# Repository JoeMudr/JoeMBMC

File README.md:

# JoeM BMC
Originally called "JoeM BMS" is now called "JoeM BMC" Battery Management Controller. Since it's not a complete BMS but only a controller for existing BMS-Modules.
This is the updated version for Teensy 4.0

This project is derived from [Toms SimpBMS code](https://github.com/Tom-evnut). It started as a clone (Software & Hardware) but ended up completely rewritten and redesigned. But you might still find some traces to the original code.

Complete documentation coming soon.

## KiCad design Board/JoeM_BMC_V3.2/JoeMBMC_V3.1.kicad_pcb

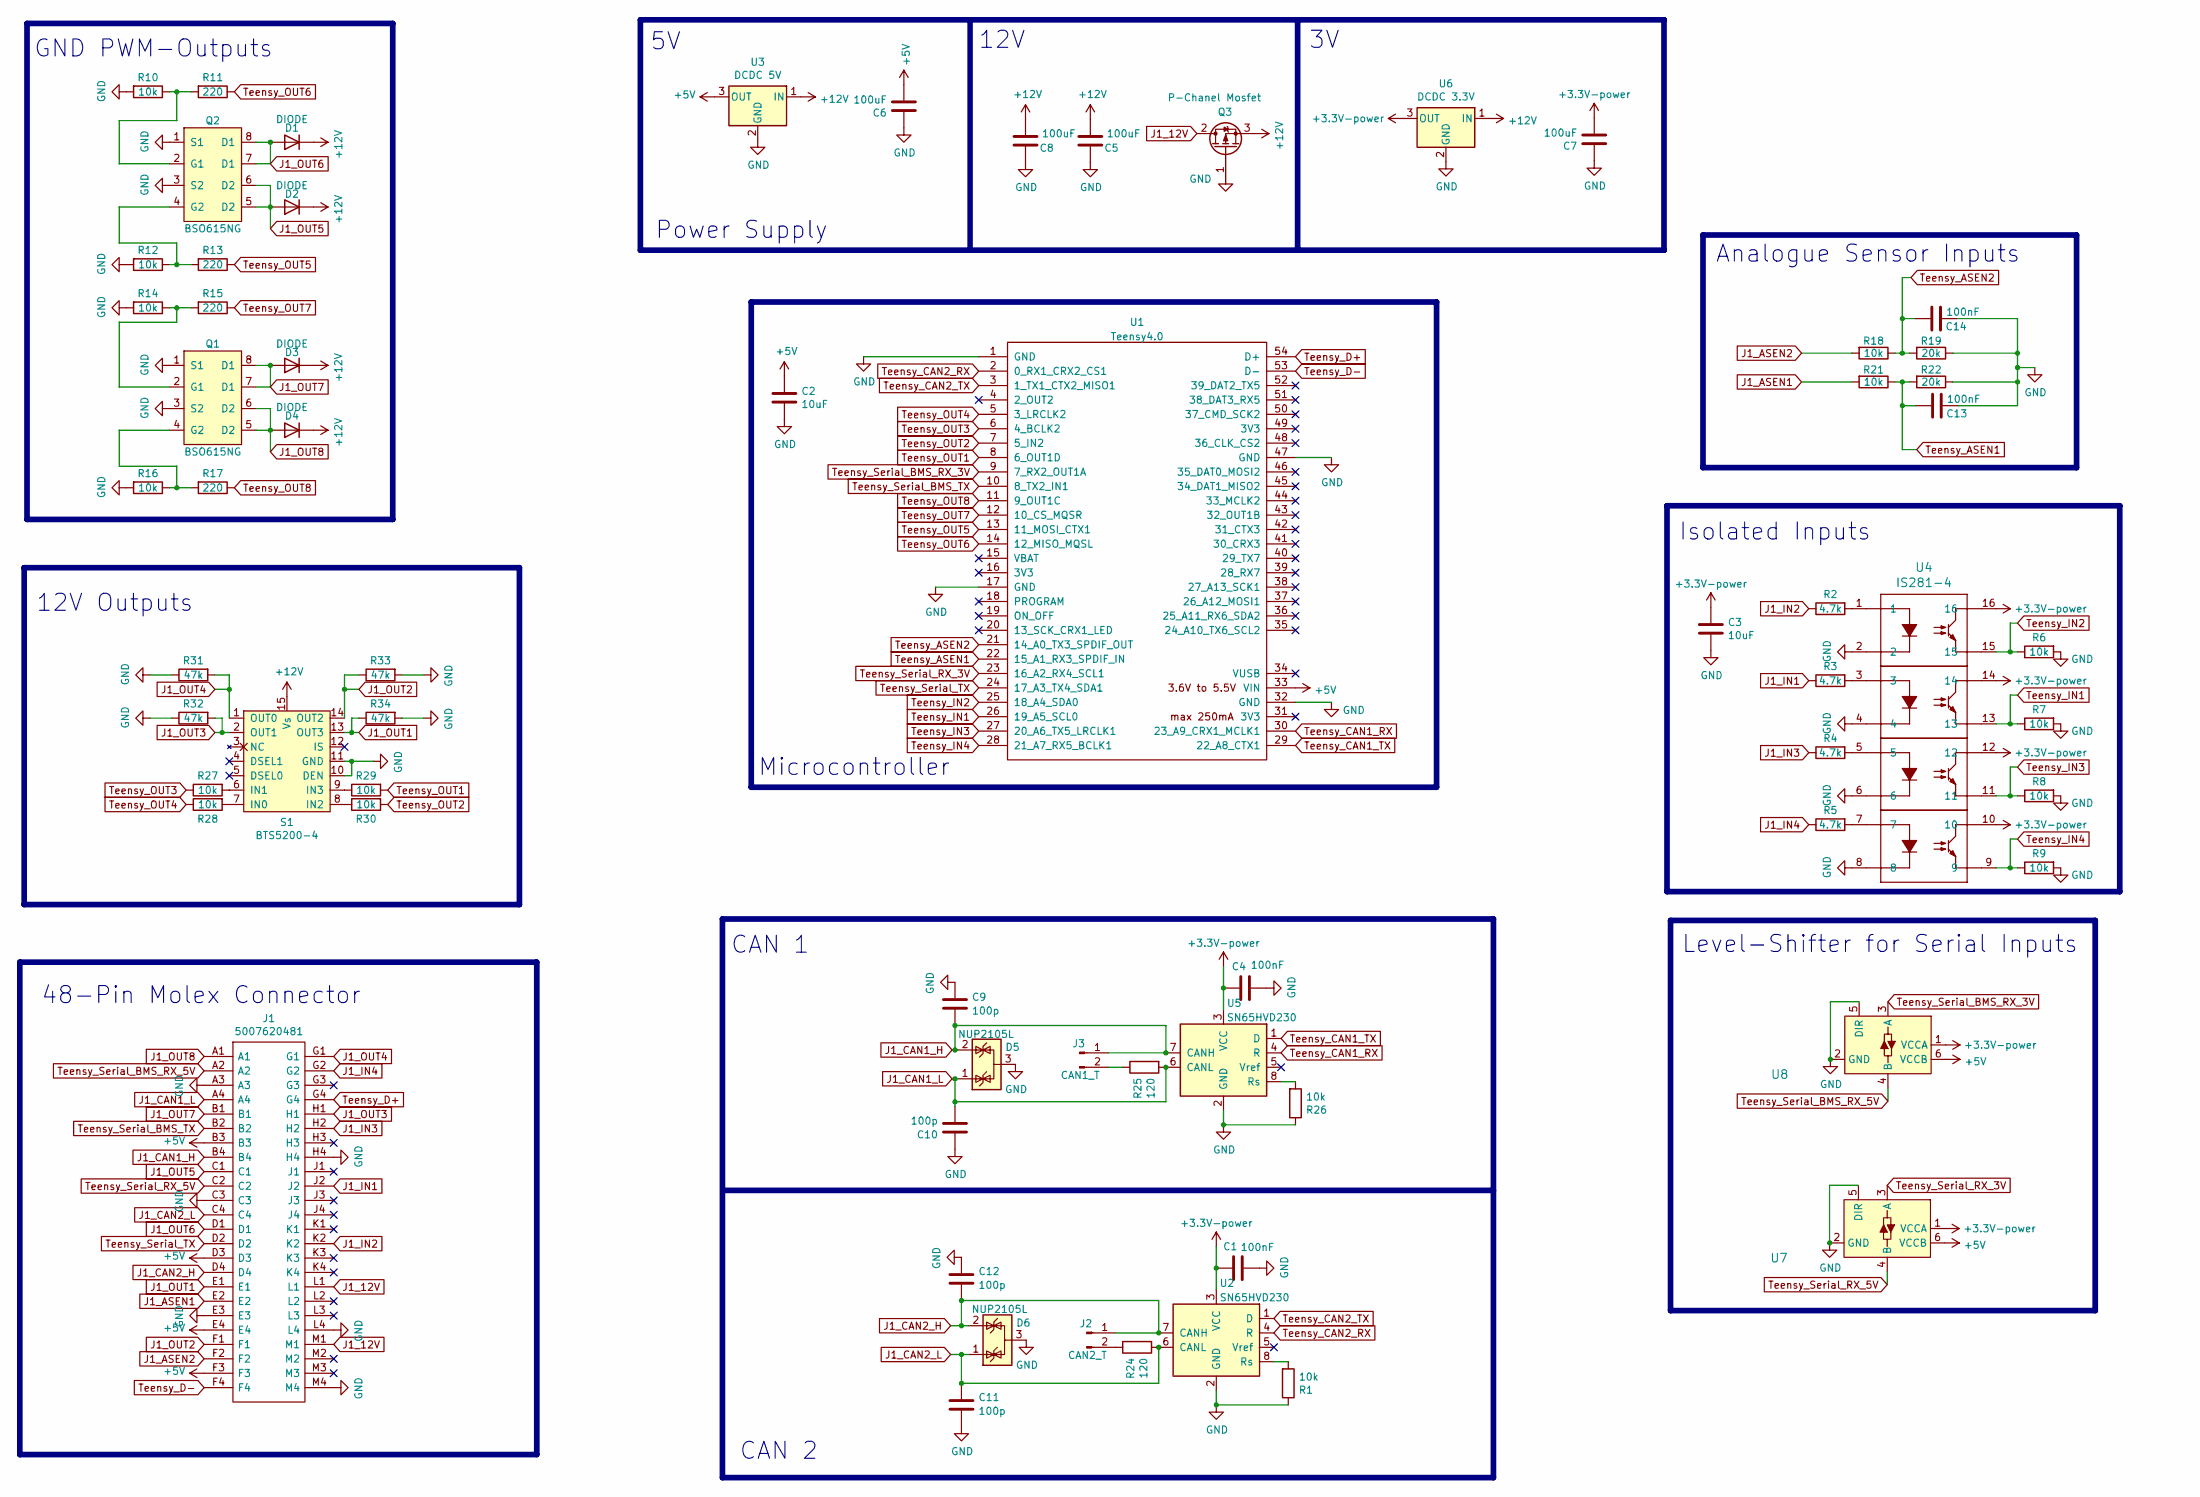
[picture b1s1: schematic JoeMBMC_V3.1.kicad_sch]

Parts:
C1, C4, C13, C14: 100nF; C_0805_2012Metric; LCSC C49678
C2, C3: 10uF; C_0805_2012Metric; LCSC C15850
C5, C6, C7, C8: 100uF; C_Elec_6.3x7.7; LCSC C3001246
C9, C10, C11, C12: 100p; C_0402_1005Metric; LCSC C1546
D1, D2, D3, D4: DIODE; D_SOD-123F; LCSC C8598
D5, D6: NUP2105L; SOT-23; LCSC C284104
J1: 5007620481; Manufacturer_Part_Number 5007620481
J2: CAN2_T; PinHeader_1x02_P2.54mm_Vertical
J3: CAN1_T; PinHeader_1x02_P2.54mm_Vertical
Q1, Q2: BSO615NG; SO-8_IRF956; LCSC C693398
Q3: P-Chanel Mosfet; TO-252-2; LCSC C416264
R1, R6, R7, R8, R9, R10, R12, R14, R16, R18, R21, R26, R27, R28, R29, R30: 10k; R_0805_2012Metric; LCSC C17414
R2, R3, R4, R5: 4.7k; R_0805_2012Metric; LCSC C17673
R11, R13, R15, R17: 220; R_0805_2012Metric; LCSC C17557
R19, R22: 20k; R_0805_2012Metric; LCSC C4328
R24, R25: 120; R_0805_2012Metric; LCSC C17437
R31, R32, R33, R34: 47k; R_0805_2012Metric; LCSC C17713
S1: BTS5200-4; PG-DSO-14-40_EP; LCSC C534815
U1: Teensy4.0; Teensy40_JoeMBMS
U2, U5: SN65HVD230; SOIC-8_3.9x4.9mm_P1.27mm; LCSC C12084
U3: DCDC 5V; Converter_DCDC_RECOM_R-78E-0.5_THT
U4: IS281-4; TLP293-4; LCSC C89878
U6: DCDC 3.3V; Converter_DCDC_RECOM_R-78E-0.5_THT
U7, U8: Level Shifter 5V to 3V; SOT-23-6; LCSC C7843

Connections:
+3V3: C1.2, C3.2, C4.2, C7.1, U2.3 (VCC), U4.10, U4.12, U4.14, U4.16, U5.3 (VCC), U6.3 (OUT), U7.1 (VCCA), U8.1 (VCCA); also elsewhere on the board
+5V: C2.2, C6.1, J1.B3, J1.D3, J1.E4, J1.F3, U1.33 (VIN), U3.3 (OUT), U7.6 (VCCB), U8.6 (VCCB); also elsewhere on the board
+12V: C5.1, C8.1, D1.1 (K), D2.1 (K), D3.1 (K), D4.1 (K), Q3.3 (S), S1.15 (Vs), U3.1 (IN), U6.1 (IN); also elsewhere on the board
GND: C1.1, C2.1, C3.1, C4.1, C5.2, C6.2, C7.2, C8.2, C9.1, C10.1, C11.2, C12.1, C13.1, C14.1, D5.3 (A), D6.3 (A), J1.A3, J1.C3, J1.E3, J1.H4, J1.L4, J1.M4, Q1.1 (S1), Q1.3 (S2), Q2.1 (S1), Q2.3 (S2), Q3.1 (G), R1.1, R6.2, R7.2, R8.2, R9.2, R10.2, R12.2, R14.2, R16.2, R19.1, R22.1, R26.1, R31.1, R32.1, R33.2, R34.2, S1.10 (DEN), S1.11 (GND), U1.1 (GND), U1.17 (GND), U1.32 (GND), U1.47 (GND), U2.2 (GND), U3.2 (GND), U4.2, U4.4, U4.6, U4.8, U5.2 (GND), U6.2 (GND), U7.2 (GND), U7.5 (DIR), U8.2 (GND), U8.5 (DIR)
J1_12V: J1.L1, J1.M1, Q3.2 (D)
J1_ASEN1: J1.E2, R21.2
J1_ASEN2: J1.F2, R18.2
J1_CAN1_H: C9.2, D5.2 (K), J1.B4, J3.1, U5.7 (CANH)
J1_CAN1_L: C10.2, D5.1 (K), J1.A4, R25.2, U5.6 (CANL)
J1_CAN2_H: C12.2, D6.2 (K), J1.D4, J2.1, U2.7 (CANH)
J1_CAN2_L: C11.1, D6.1 (K), J1.C4, R24.2, U2.6 (CANL)
J1_IN1: J1.J2, R3.1
J1_IN2: J1.K2, R2.1
J1_IN3: J1.H2, R4.1
J1_IN4: J1.G2, R5.1
J1_OUT1: J1.E1, R34.1, S1.13 (OUT3)
J1_OUT2: J1.F1, R33.1, S1.14 (OUT2)
J1_OUT3: J1.H1, R32.2, S1.2 (OUT1)
J1_OUT4: J1.G1, R31.2, S1.1 (OUT0)
J1_OUT5: D2.2 (A), J1.C1, Q2.5 (D2), Q2.6 (D2)
J1_OUT6: D1.2 (A), J1.D1, Q2.7 (D1), Q2.8 (D1)
J1_OUT7: D3.2 (A), J1.B1, Q1.7 (D1), Q1.8 (D1)
J1_OUT8: D4.2 (A), J1.A1, Q1.5 (D2), Q1.6 (D2)
unnamed: J2.2, R24.1
unnamed: J3.2, R25.1
unnamed: Q1.2 (G1), R14.1, R15.2
unnamed: Q1.4 (G2), R16.1, R17.2
unnamed: Q2.2 (G1), R10.1, R11.2
unnamed: Q2.4 (G2), R12.1, R13.2
unnamed: R2.2, U4.1
unnamed: R3.2, U4.3
unnamed: R4.2, U4.5
unnamed: R5.2, U4.7
unnamed: R28.2, S1.7 (IN0)
unnamed: R27.2, S1.6 (IN1)
unnamed: R30.1, S1.8 (IN2)
unnamed: R29.1, S1.9 (IN3)
unnamed: R1.2, U2.8 (Rs)
unnamed: R26.2, U5.8 (Rs)
Teensy_ASEN1: C13.2, R21.1, R22.2, U1.22 (15_A1_RX3_SPDIF_IN)
Teensy_ASEN2: C14.2, R18.1, R19.2, U1.21 (14_A0_TX3_SPDIF_OUT)
Teensy_CAN1_RX: U1.30 (23_A9_CRX1_MCLK1), U5.4 (R)
Teensy_CAN1_TX: U1.29 (22_A8_CTX1), U5.1 (D)
Teensy_CAN2_RX: U1.2 (0_RX1_CRX2_CS1), U2.4 (R)
Teensy_CAN2_TX: U1.3 (1_TX1_CTX2_MISO1), U2.1 (D)
Teensy_D+: J1.G4, U1.54 (D+)
Teensy_D-: J1.F4, U1.53 (D-)
Teensy_IN1: R7.1, U1.26 (19_A5_SCL0), U4.13
Teensy_IN2: R6.1, U1.25 (18_A4_SDA0), U4.15
Teensy_IN3: R8.1, U1.27 (20_A6_TX5_LRCLK1), U4.11
Teensy_IN4: R9.1, U1.28 (21_A7_RX5_BCLK1), U4.9
Teensy_OUT1: R29.2, U1.8 (6_OUT1D)
Teensy_OUT2: R30.2, U1.7 (5_IN2)
Teensy_OUT3: R27.1, U1.6 (4_BCLK2)
Teensy_OUT4: R28.1, U1.5 (3_LRCLK2)
Teensy_OUT5: R13.1, U1.13 (11_MOSI_CTX1)
Teensy_OUT6: R11.1, U1.14 (12_MISO_MQSL)
Teensy_OUT7: R15.1, U1.12 (10_CS_MQSR)
Teensy_OUT8: R17.1, U1.11 (9_OUT1C)
Teensy_Serial_BMS_RX_3V: U1.9 (7_RX2_OUT1A), U8.3 (A)
Teensy_Serial_BMS_RX_5V: J1.A2, U8.4 (B)
Teensy_Serial_BMS_TX: J1.B2, U1.10 (8_TX2_IN1)
Teensy_Serial_RX_3V: U1.23 (16_A2_RX4_SCL1), U7.3 (A)
Teensy_Serial_RX_5V: J1.C2, U7.4 (B)
Teensy_Serial_TX: J1.D2, U1.24 (17_A3_TX4_SDA1)

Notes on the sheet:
Analogue Sensor Inputs
GND PWM-Outputs
48-Pin Molex Connector
CAN 2
CAN 1
12V Outputs
Isolated Inputs
Microcontroller
Power Supply
12V
Level-Shifter for Serial Inputs

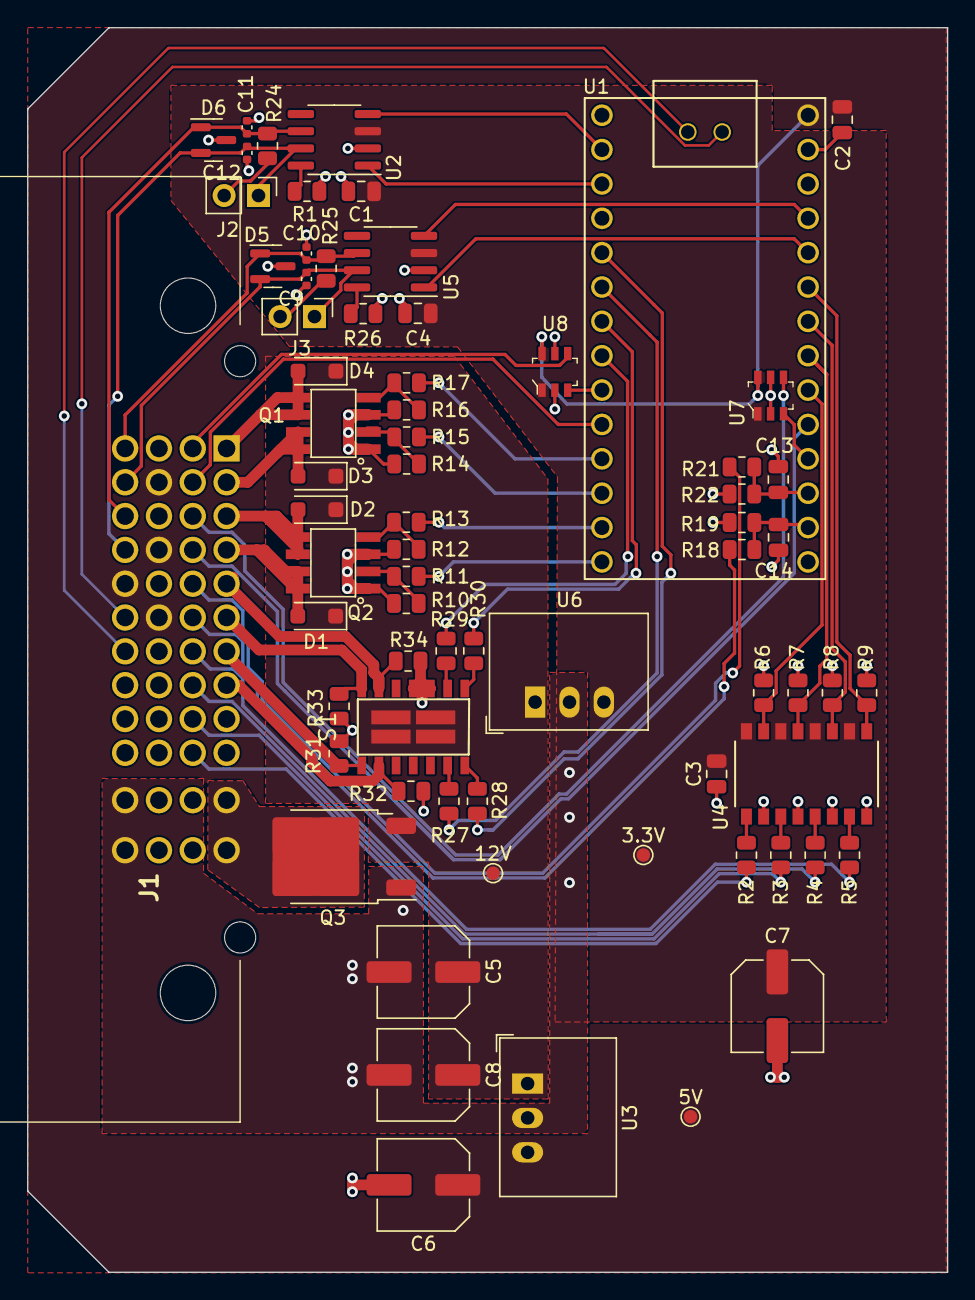
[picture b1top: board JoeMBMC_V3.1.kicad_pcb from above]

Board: 2 copper layers, 68.0 x 92.0 mm, 70 parts (0 on the bottom side), 65 nets.

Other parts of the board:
3.3V, 5V, 12V: TestPoint_Pad_D1.0mm

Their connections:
+3V3: 3.3V.1; also elsewhere on the board
+5V: 5V.1; also elsewhere on the board
+12V: 12V.1; also elsewhere on the board

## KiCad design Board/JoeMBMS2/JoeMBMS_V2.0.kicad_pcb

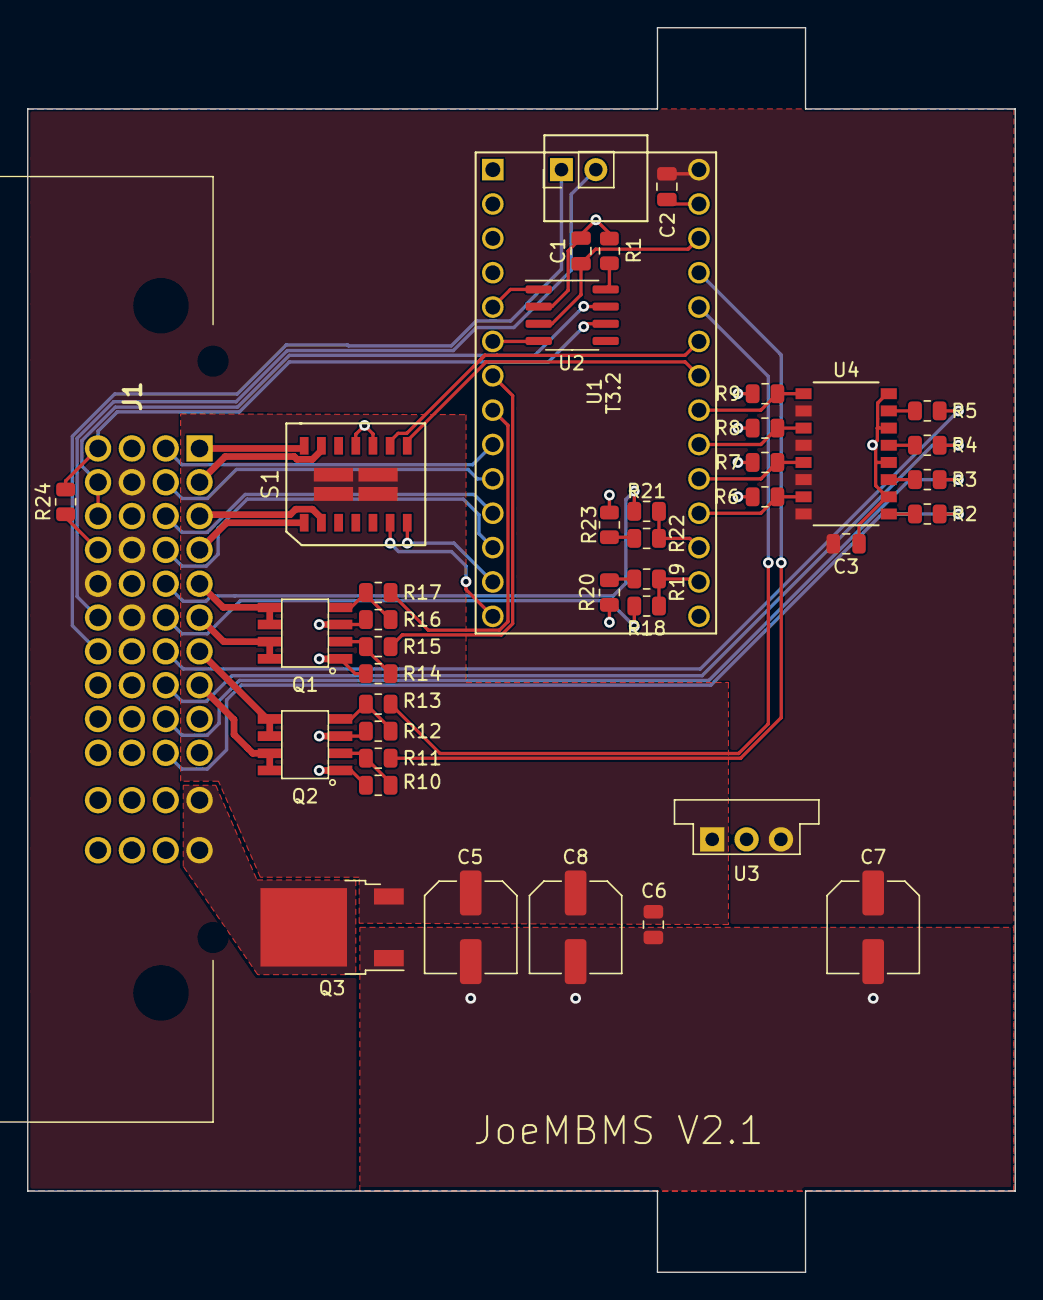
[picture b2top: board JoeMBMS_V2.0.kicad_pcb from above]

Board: 2 copper layers, 73.0 x 92.0 mm, 40 parts (0 on the bottom side), 53 nets.

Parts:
C1: 100nF; C_0805_2012Metric
C2, C3, C6: 10uF; C_0805_2012Metric
C5, C7, C8: 100uF; C_Elec_6.3x7.7
J1: 5007620481
Q1, Q2: BSO615NG; SO-8_IRF956
Q3: P-Chanel Mosfet; TO-252-2
R1, R6, R7, R8, R9, R10, R12, R14, R16, R18, R19, R20, R21, R22, R23: 10k; R_0805_2012Metric
R2, R3, R4, R5: 4.7k; R_0805_2012Metric
R11, R13, R15, R17: 220; R_0805_2012Metric
R24: 120; R_0805_2012Metric
S1: BTS5200-4; PG-DSO-14-40_EP
U1: Teensy3.2; Teensy30_31_32_LC_Mod
U2: SN65HVD230; SOIC-8_3.9x4.9mm_P1.27mm
U3: DCDC 5V; Converter_DCDC_muRata_OKI-78SR_Vertical
U4: IS281-4; TLP293-4

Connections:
+3V3: C1.2, U1.31, U2.3
+12V: C5.1, C6.2, C8.1, Q3.3, S1.15, U3.1
GND: C1.1, C2.1, C3.1, C5.2, C6.1, C7.2, C8.2, J1.A3, J1.C3, J1.E3, J1.H4, J1.L4, J1.M4, Q1.1, Q1.3, Q2.1, Q2.3, Q3.1, R1.1, R6.2, R7.2, R8.2, R9.2, R10.2, R12.2, R14.2, R16.2, R20.1, R23.1, S1.10, S1.11, U1.1, U1.32, U2.2, U3.2, U4.2, U4.4, U4.6, U4.8
J1_12V: J1.L1, J1.M1, Q3.2
J1_ASEN1: J1.E2, R21.2
J1_ASEN2: J1.F2, R18.2
J1_CANH: J1.B4, J1.C4, U2.7
J1_CANL: J1.A4, R24.2, U2.6
J1_CAN_T_2: J1.D4, R24.1
J1_IN1: J1.J2, R3.1
J1_IN2: J1.K2, R2.1
J1_IN3: J1.H2, R4.1
J1_IN4: J1.G2, R5.1
J1_OUT1: J1.D1, S1.1
J1_OUT2: J1.C1, S1.2
J1_OUT3: J1.A1, S1.14
J1_OUT4: J1.B1, S1.13
J1_OUT5: J1.G1, Q2.5, Q2.6
J1_OUT6: J1.H1, Q2.7, Q2.8
J1_OUT7: J1.F1, Q1.7, Q1.8
J1_OUT8: J1.E1, Q1.5, Q1.6
J1_RX2: J1.C2, U1.11
J1_TX2: J1.D2, U1.12
unnamed: Q1.2, R14.1, R15.2
unnamed: Q1.4, R16.1, R17.2
unnamed: Q2.2, R10.1, R11.2
unnamed: Q2.4, R12.1, R13.2
unnamed: R1.2, U2.8
unnamed: R2.2, U4.1
unnamed: R3.2, U4.3
unnamed: R4.2, U4.5
unnamed: R5.2, U4.7
unnamed: R19.1, R20.2
unnamed: R22.1, R23.2
Teensy_ASEN1: R21.1, R22.2, U1.22
Teensy_ASEN2: R18.1, R19.2, U1.21
Teensy_IN1: R7.1, U1.24, U4.13
Teensy_IN2: R6.1, U1.23, U4.15
Teensy_IN3: R8.1, U1.25, U4.11
Teensy_IN4: R9.1, U1.26, U4.9
Teensy_OUT1: S1.7, U1.13
Teensy_OUT2: S1.6, U1.14
Teensy_OUT3: S1.8, U1.27
Teensy_OUT4: S1.9, U1.28
Teensy_OUT5: R13.1, U1.29
Teensy_OUT6: R11.1, U1.30
Teensy_OUT7: R15.1, U1.7
Teensy_OUT8: R17.1, U1.8
Teensy_RX: U1.6, U2.4
Teensy_RX3: J1.A2, U1.9
Teensy_TX: U1.5, U2.1
Teensy_TX3: J1.B2, U1.10
Teensy_VUSB: C2.2, C3.2, C7.1, J1.B3, J1.D3, J1.E4, J1.F3, U1.33, U3.3, U4.10, U4.12, U4.14, U4.16

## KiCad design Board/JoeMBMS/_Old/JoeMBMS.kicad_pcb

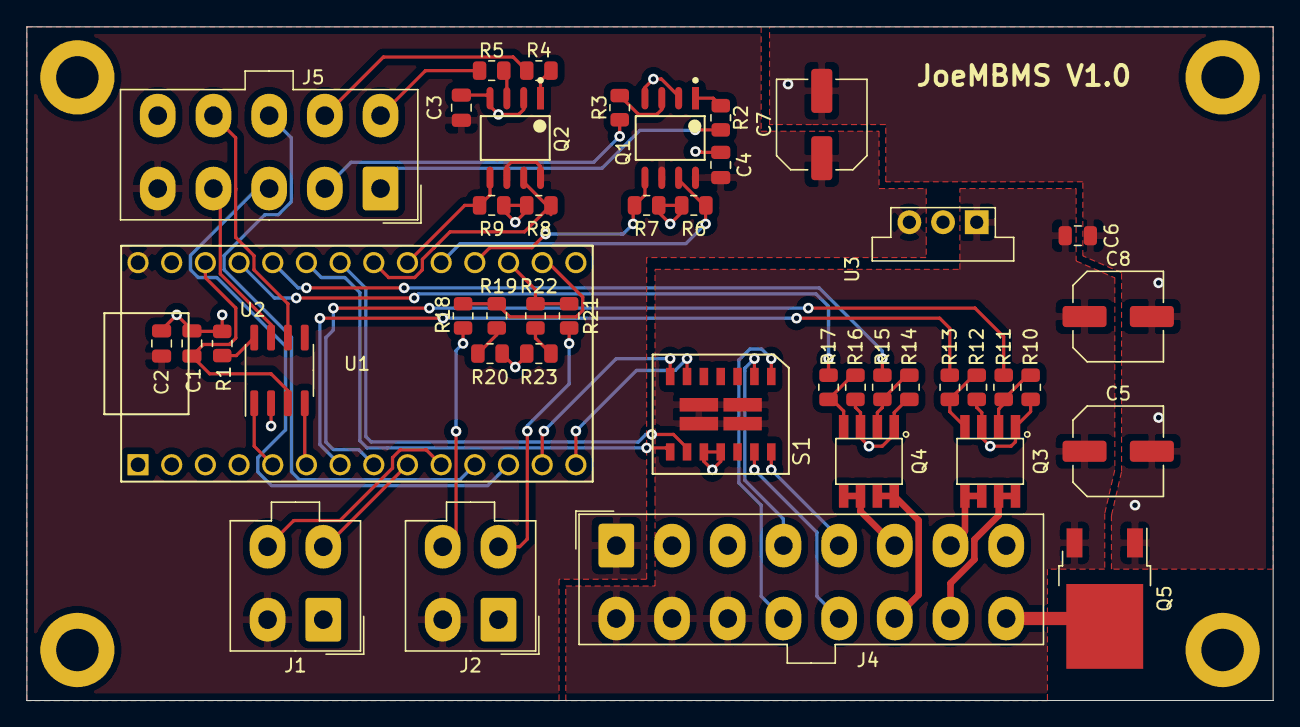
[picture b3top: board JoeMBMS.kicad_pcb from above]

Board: 2 copper layers, 94.0 x 50.8 mm, 44 parts (0 on the bottom side), 52 nets.

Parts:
C1: 100nF; C_0805_2012Metric
C2, C3, C4, C6: 10uF; C_0805_2012Metric
C5, C7, C8: 100uF; C_Elec_6.3x7.7
J1: Tesla_BMS; Molex_Mini-Fit_Jr_5566-04A_2x02_P4.20mm_Vertical
J2: Analog_Sens; Molex_Mini-Fit_Jr_5566-04A_2x02_P4.20mm_Vertical
J4: OUT_PWR; Molex_Mini-Fit_Jr_5566-16A_2x08_P4.20mm_Vertical
J5: IN_COMM; Molex_Mini-Fit_Jr_5566-10A_2x05_P4.20mm_Vertical
Q1, Q2: ACPL-227-500E; Broadcom-SO-8-0-0-IPC_C_
Q3, Q4: IRF9956; SO-8_IRF956
Q5: 068P03L; TO-252-2
R1, R6, R7, R8, R9, R10, R12, R14, R16, R18, R19, R20, R21, R22, R23: 10k; R_0805_2012Metric
R2: 4.7K; R_0805_2012Metric
R3, R4, R5: 4.7k; R_0805_2012Metric
R11, R13, R15, R17: 220; R_0805_2012Metric
S1: BTS5200-4; PG-DSO-14-40_EP
U1: Teensy3.2; Teensy30_31_32_LC_Mod
U2: SN65HVD230; SOIC-8_3.9x4.9mm_P1.27mm
U3: DCDC 5V; Converter_DCDC_muRata_OKI-78SR_Vertical

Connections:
+3V3: C1.2, U1.31, U2.3
+5V: C2.2, C3.2, C4.2, C7.1, J1.2, J2.2, J4.1, J5.5, Q1.6, Q1.8, Q2.6, Q2.8, U1.33, U3.3
+12V: C5.1, C6.2, C8.1, J4.9, J4.10, J4.11, Q5.3, S1.15, U3.1
GND: C1.1, C2.1, C3.1, C4.1, C5.2, C6.1, C7.2, C8.2, J1.1, J2.1, J4.2, J4.3, J4.8, J5.10, Q1.2, Q1.4, Q2.2, Q2.4, Q3.1, Q3.3, Q4.1, Q4.3, Q5.1, R1.1, R6.2, R7.2, R8.2, R9.2, R10.2, R12.2, R14.2, R16.2, R20.1, R23.1, S1.10, S1.11, U1.1, U1.32, U2.2, U3.2
J4_12V: J4.16, Q5.2
J4_OUT1: J4.12, S1.1
J4_OUT2: J4.4, S1.2
J4_OUT3: J4.13, S1.13
J4_OUT4: J4.5, S1.14
J4_OUT5: J4.14, Q4.7, Q4.8
J4_OUT6: J4.6, Q4.5, Q4.6
J4_OUT7: J4.7, Q3.5, Q3.6
J4_OUT8: J4.15, Q3.7, Q3.8
J5_CANH: J5.4, U2.7
J5_CANL: J5.9, U2.6
J5_IN1: J5.1, R2.1
J5_IN2: J5.2, R3.1
J5_IN3: J5.6, R5.1
J5_IN4: J5.7, R4.1
J5_RX2: J5.8, U1.11
J5_TX2: J5.3, U1.12
unnamed: J2.3, R21.2
unnamed: J2.4, R18.2
unnamed: Q1.1, R2.2
unnamed: Q1.3, R3.2
unnamed: Q2.1, R4.2
unnamed: Q2.3, R5.2
unnamed: Q3.2, R10.1, R11.2
unnamed: Q3.4, R12.1, R13.2
unnamed: Q4.2, R14.1, R15.2
unnamed: Q4.4, R16.1, R17.2
unnamed: R1.2, U2.8
unnamed: R19.1, R20.2
unnamed: R22.1, R23.2
Teensy_ASEN1: R21.1, R22.2, U1.22
Teensy_ASEN2: R18.1, R19.2, U1.21
Teensy_IN1: Q1.7, R6.1, U1.24
Teensy_IN2: Q1.5, R7.1, U1.23
Teensy_IN3: Q2.5, R9.1, U1.25
Teensy_IN4: Q2.7, R8.1, U1.26
Teensy_OUT1: S1.7, U1.13
Teensy_OUT2: S1.6, U1.14
Teensy_OUT3: S1.9, U1.27
Teensy_OUT4: S1.8, U1.28
Teensy_OUT5: R15.1, U1.29
Teensy_OUT6: R17.1, U1.30
Teensy_OUT7: R13.1, U1.7
Teensy_OUT8: R11.1, U1.8
Teensy_RX: U1.6, U2.4
Teensy_RX3: J1.3, U1.9
Teensy_TX: U1.5, U2.1
Teensy_TX3: J1.4, U1.10

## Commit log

2023-04-18 test
2023-04-18 Initial
2023-04-18 old Workspace deleted
2023-04-18 clean old Board files
2023-10-21 Upgrade Teensy 3.2 -> 4.0
2023-10-21 cleanup
2023-10-21 add CAB300 CAN IDs
2023-11-11 Board Updates for 3.3V
2023-11-25 Version
2023-11-26 remove Software CAN
2023-11-26 Rename & Cleanup
2023-11-26 Git Test
2023-12-02 remove zener on analogue sensor inputs
2023-12-18 prepare for CAN2
2023-12-20 CAN rearrange & debug, Gauge-Fix
2024-01-02 change Alerts/Warnings accordung to SMA Doc.
2024-01-02 Board Backups
2024-01-02 Check for ChargerDirect in vehicle mode
2024-01-06 Console Bugfix
2024-01-06 Teensy moved; USB clearance
2024-01-08 modify CAP_Temp_Alteration
2024-01-08 modify CAP_Temp_alt.
2024-01-08 Board redesign
2024-01-08 Warn_handle() does no use the correct warning values #19
2024-01-08 make BalanceCells_Check() return value 0 or 1 #20
2024-01-08 remove unused variable "cellsbalancing"
2024-01-08 add second dimenson to CAN_Map
2024-01-08 intervall added to CAN_MAP #17
2024-01-09 #16 start adding VW BMS
2024-01-24 Complete rewrite of BMS-Libs for #16, VW & Tesla S/X included
2024-01-27 first implementation of BMW CMU #16
2024-01-28 eliminate float variables, minor changes
2024-01-28 remove mWs
2024-01-28 outsource CANOpen, minor fixes, cleanup some ToDos
2024-02-05 USB-Flex-Board
2024-02-05 minor fixes: abs -> labs; current without floats; fixes in Menu (former floats); fix constrains; add ReadTimeout
2024-02-05 move BMS timeout to BMSManager; float -> double typecast for 32bit values; restructure SOC_update()
2024-02-05 rearranging debug output; reset values in BMSinit() to use BMSinit() as reset.
2024-02-05 underclock; minor twaeks
2024-02-17 replace print/println by printf
2024-02-17 USB traces closer together
2024-02-18 fix Reboot; adjust debug output; add binary conversion
2024-02-18 firmver
2024-02-18 test2
2024-02-18 rename
2024-02-18 License
2024-02-18 Create LICENSE
2024-02-18 Readme
2024-03-13 fixes: Display, SOH
2024-03-13 Board Updates
2024-03-22 modify BMS poll for BMW i3
2024-03-22 Documentation
2024-03-24 prepare #23; add value change check für current sensors.
2024-03-24 Fixes: SOC calc; TSensors Average
2024-03-24 Fix: ModuleCnt reset
2024-03-24 Fixes: Display; Serial clear
2024-03-24 Readme update
2024-03-24 Doc: FW-Update; Terminal
2024-03-24 Docu update
2024-03-24 Start Add Pyliontech HV CAN protocol #23
2024-03-24 Display layout fixes
2024-03-26 Move BMC_Std_send to Statemachine; minor changes
2024-03-27 Add TCU Comm; Fixes: AVGTemp, Balancing Stop.
2024-03-27 Reduced CANStruct size; removed some global variables in BMSManager
2024-03-29 Add separate Charge/discharge Limits #14
2024-03-29 #18 prev. commit with wrong issue nr.
2024-03-29 Update 240329
2024-03-30 Fixes: Alarms&Warnings bits missing; Restructure CondChecks; Add State Stat_Discharge -> ESS, CondCheck
2024-03-30 Rearrange config; rename variables; move comments to config; add hotkeys for OUT / Modules display
2024-03-30 Update BIN 240330
2024-03-30 some OCD
2024-04-10 prpare for #11
2024-04-27 Fix for HV-CAN-Protocol: Wrong Temp conversion
2024-04-27 Board: removed old Backups
2024-04-28 fix ETA; remove CAN_BMC_Std from Stat_Charged; Fix CurrentAVG; Fix CAN-HV-Protocl current
2024-04-29 Degug no alarms for pylontech
2024-04-29 Fix Pylontech HV Under Temp issue
2024-05-02 disabled 16A Limit
2024-05-22 Balancing Fix
2024-05-22 board Backup cleanup
2024-05-23 TCU CAN ID to 0x7FF
2024-06-01 Menu option for Battery ID; Battery ID added to HV CAN messages; additional value types for menu options
2024-06-01 Update BIN; Version Update
2024-06-03 prepare dynamic secondary Serial (BT)
2024-06-14 restructure Folder
2024-06-28 cleanup includes; fix dynamic Serial
2024-06-28 fix includes; add Power in CAN ID 379
2024-10-06 Rename Statemachine; Add CAN-Bus charge indication
2024-10-06 documentation Update
2024-10-06 Board revisions
2024-10-20 Doc: Max-Voltages reduced for Mosfet.
2024-10-20 Fix moduleReadCnt; Try adding BOD; make vars local,static if possible; Add SOC to Settings struct; change Serial Read to string & trim(); rename some vars
2024-10-20 no changes
2024-10-20 removed Board Backups & Putty Logs
2024-10-20 Changed Profile Name
2024-10-20 remove seral read from Menu()
2024-10-20 make Currentavg_calc vars private static; assign HVIL to IN4; changes to current display on debug screen.
2024-10-20 cosmetic changes
2024-10-27 fix ETA / currentavg_calc()
2024-10-27 #28 add "blinking" to Errors/Warnings
2024-11-03 move clearCANStruct() into header file for global usage.
2024-11-03 add "Balance enable" as output option. not active jet.
2024-12-02 fix PWM Contactor control; simplify CAN_SEN_read()
2024-12-06 Fix missing Outputs in Stat_Charge
2024-12-20 add Stat_Discharge for display
2024-12-20 Update Display
2024-12-26 Add ChargeCurrentLimit() ti Stat_Drive; fix ChargeCurrentLimit; Add TLow-Check to DischargeCurrentLimit()
2024-12-28 ChargeCurrentLimit(): use smaler Value from ChargerChargeCurrentMax or ChargeOverCurrAlarm
2025-01-06 Added Uptime; Added AlarmDischargeHyst for heating / cooling; restructured Battery menu
2025-01-12 cleanup; Add Power (mW) to debug screen.
2025-01-31 charge / dischargecurrent mapping oflerflow fixed
2025-01-31 Version push
2025-02-02 Change Battery Menu Temperature layout
2025-02-02 revert csv.cpp
2025-02-02 non-linear charge derating
2025-02-02 Stat_Charged added to ESS mode
2025-02-02 add charge hysteresis for stat_charged in ESS mode
2025-02-02 comment fix
2025-02-02 modified ESS precharged funktion; Added contactors ON to Stat_Charged ESS mode
2025-02-09 fix ESS_CondCheck; expand chargecurrent taper to full hysteresis
2025-02-22 Fix balancing not resetting (Tesla); Fix balancing missing output (VW MEB)
2025-02-22 bump firmware version
2025-02-22 Fix chargecurrentfactor
2025-03-09 slowly increase charge current after 0A
2025-03-09 bumpf Firmver.
2025-03-23 remove 30 chargecurrent taoering for current feedbackloop.
